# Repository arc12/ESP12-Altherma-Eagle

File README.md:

# ESP12 PCB for ESPAltherma

## Power
The normal use case, i.e. operating in the HP, is for the HP to power the board. JP1 is effectively an emergency disconnect feature and is normally on.

## Flashing
The firmware supports "Over The Air" updating but initial flashing will be via the Serial header. This initial flashing should be done without X10A being connected to the heat pump.

If testing with a 5V USB/Serial adapter attached to X10A then JP2 should be removed.

## Runtime Switches
__S1__ (Reset) - ESP-12 reset.
__S2__ is optional, see notes on Serial, below

## Headers
### Serial
UART pins and power, intended for initial flashing the device and diagnostic monitoring using a BT module. When using a Bluetooth serial monitor, JP2 should be on, to supply it with power. Note that the pin labels are to match those on the serial device, rather than being those of the ESP8622.  3.3V logic must be used.

Note that, if the DTR and RTS signals are connected (and D2 installed), then the PlatformIO monitor (or any other serial interaction which is not bootloading) must be configured as follows (add to platformio.ini), otherwise attempts to use the Monitor cause the board to hang (recovers if the monitor is killed):
```
monitor_rts = 0
monitor_dtr = 0
```

If DTR is not available on the USB/Serial adapter, install S2 and R16 and cut through SJ1 and SJ2 for manual boot-loader trigger.
__S2__ (Flash) -  Reset will trigger the boot loader if this switch is held on (i.e. flashing is done by holding S2 and then pressing/releasing S1). Once the new programme has been flashed, S1 (reset) must be done manually.

## Off-board "Thermo" Relay
See the ESPAltherma documentation for notes on the use of a relay to simulate a thermostat in order to on/off control the HP. This is a mains voltage relay AFAIK and in the interest of safety I decided to keep mains off the PCB. Hence there is a header to connect the GPIO to an off-board relay (which should ideally have an opto-coupler and suitable isolation gaps). A solder-jumper (SJ3) is used to allow selection of 3.3V or 5V for the header.

## Options
### LED Signalling
The battery of LEDs and associated Rs, plus JP3 allow for the output states to be signalled. JP3 allows for this signalling to be disconnected/reconnected as required. The external "thermo" relay is assumed to have its own signal.

If the LEDs are not fitted then the pad nearest to "L1", "SG1", etc may be used as a test point.

The ESP-12 modules have a LED on GPIO2, which is used as a "booted and running OK" signal.

### Bluetooth Monitoring
May be achieved by connecting a BT Serial module to the Serial header. Connect JP2 to power the module. NB this is 3.3V.

### Smart Grid OR Power Limitation
These two features use the same GPIO; only fit one set of components!

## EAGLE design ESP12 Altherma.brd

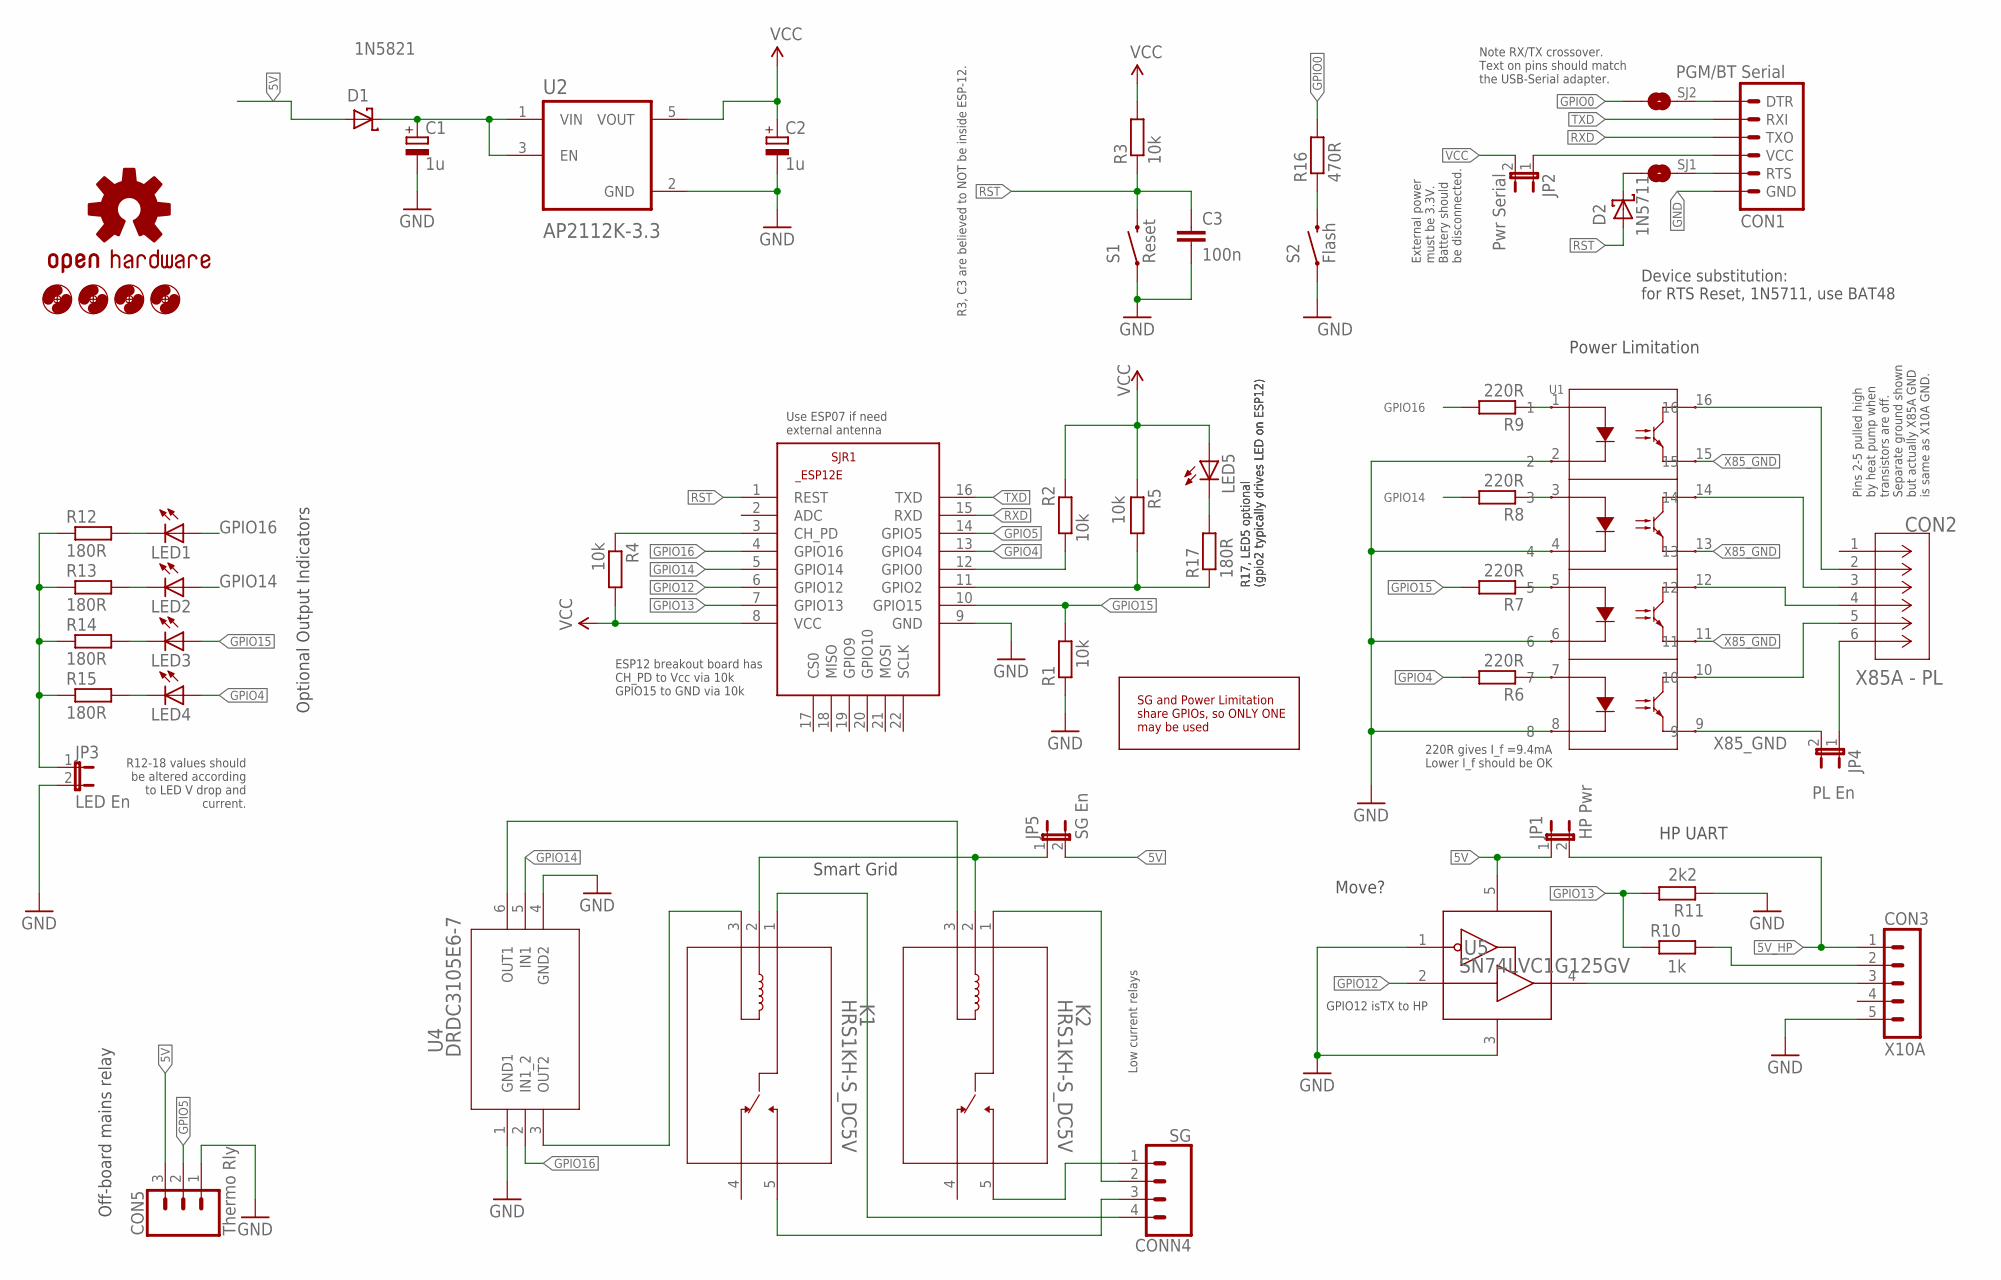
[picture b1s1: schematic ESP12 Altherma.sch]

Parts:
C1, C2: 1u; E2,5-5
C3: 100n; 1206
CON1: PGM/BT Serial; 1X06-KIT
CON2: X85A - PL; CONN_B06B-PASK_JST
CON3: X10A; B5B-EH-A
CON5: Thermo Rly; 1X03
CONN4: SG; 1X04
D1: 1N5821; DO201-15
D2: 1N5711; DO35-7
H1, H2, H3, H4: MOUNT-HOLE3.2; 3,2
JP1: HP Pwr; 1X02
JP2: Pwr Serial; 1X02
JP3: LED En; 1X02
JP4: PL En; 1X02
JP5: SG En; 1X02
K1, K2: HRS1KH-S_DC5V; HRS1KH-S_DC5V_MTC
LED1, LED2, LED3, LED4, LED5: LED1206; LED-1206
LOGO1: OSHW-LOGOM; OSHW-LOGO-M
R1, R2, R3, R4, R5: 10k; 1206
R6, R7, R8, R9: 220R; 1206
R10: 1k; 1206
R11: 2k2; 1206
R12, R13, R14, R15, R17: 180R; 1206
R16: 470R; 0204/7
S1: Reset; TACTILE-PTH
S2: Flash; TACTILE-PTH
SJ1, SJ2: SOLDERJUMPERTRACE; SJ_2S-TRACE
SJR1: ESP8266-12EESP8266-ESP12E-X; ESP8266-ESP12E0-NKE
U1: TLP291-4; SO16_TOS
U2: AP2112K-3.3; SOT95P285X140-5N
U4: DRDC3105E6-7; SOT26-DI_DIO-M
U5: SN74LVC1G125GV; DBV0005A_L

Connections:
5V: CON5.3, D1.A, JP1.1, JP5.2, U5.5 (VCC)
5V_HP: CON3.1, JP1.2
GND: C1.-, C2.-, C3.2, CON1.1 (GND), CON3.5, CON5.1, JP3.2, R1.1, R11.1, S1.1, S2.1, SJR1.9 (GND), U1.2, U1.4, U1.6, U1.8, U2.2 (GND), U4.1 (GND1), U4.4 (GND2), U5.1 (OE_N), U5.3 (GND)
GPIO0: R2.1, R16.2, SJ2.1, SJR1.12 (GPIO0)
GPIO2: R5.2, R17.1, SJR1.11 (GPIO2)
GPIO4: LED4.A, R6.2, SJR1.13 (GPIO4)
GPIO5: CON5.2, SJR1.14 (GPIO5)
GPIO12: SJR1.6 (GPIO12), U5.2 (A)
GPIO13: R10.1, R11.2, SJR1.7 (GPIO13)
GPIO14: LED2.A, R8.2, SJR1.5 (GPIO14), U4.5 (IN1)
GPIO15: LED3.A, R1.2, R7.2, SJR1.10 (GPIO15)
GPIO16: LED1.A, R9.2, SJR1.4 (GPIO16), U4.2 (IN1_2)
unnamed: R16.1, S2.3 (2)
unnamed: R9.1, U1.1
unnamed: CON2.3, U1.14
unnamed: JP3.1, R12.1, R13.1, R14.1, R15.1
unnamed: CON1.2 (RTS), SJ1.2
unnamed: JP5.1, K1.2, K2.2
unnamed: LED3.C, R14.2
unnamed: C1.+, D1.C, U2.1 (VIN), U2.3 (EN)
unnamed: CON1.3 (VCC), JP2.1
unnamed: CON1.6 (DTR), SJ2.2
unnamed: CON2.5, U1.10
unnamed: CON2.4, U1.12
unnamed: CON2.2, U1.16
unnamed: D2.C, SJ1.1
unnamed: LED4.C, R15.2
unnamed: R4.1, SJR1.3 (CH_PD)
unnamed: R6.1, U1.7
unnamed: R8.1, U1.3
unnamed: R7.1, U1.5
unnamed: CON3.3, U5.4 (Y)
unnamed: CON3.2, R10.2
unnamed: CONN4.1, K2.5
unnamed: CONN4.2, K2.1
unnamed: CONN4.3, K1.5
unnamed: CONN4.4, K1.1
unnamed: K1.3, U4.3 (OUT2)
unnamed: CON2.6, JP4.1
unnamed: LED5.C, R17.2
unnamed: K2.3, U4.6 (OUT1)
unnamed: LED1.C, R12.2
unnamed: LED2.C, R13.2
RST: C3.1, D2.A, R3.1, S1.3 (2), SJR1.1 (REST)
RXD: CON1.4 (TXO), SJR1.15 (RXD)
TXD: CON1.5 (RXI), SJR1.16 (TXD)
VCC: C2.+, JP2.2, LED5.A, R2.2, R3.2, R4.2, R5.1, SJR1.8 (VCC), U2.5 (VOUT)
X85_GND: JP4.2, U1.9, U1.11, U1.13, U1.15

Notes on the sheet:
R3, C3 are believed to NOT be inside ESP-12.
ESP12 breakout board has CH_PD to Vcc via 10k GPIO15 to GND via 10k
Note RX/TX crossover. Text on pins should match the USB-Serial adapter.
External power must be 3.3V. Battery should be disconnected.
R12-18 values should be altered according to LED V drop and current.
Device substitution: for RTS Reset, 1N5711, use BAT48
GPIO12 isTX to HP
Low current relays
Use ESP07 if need external antenna
Optional Output Indicators
Power Limitation
Smart Grid
HP UART
Off-board mains relay
220R gives I_f =9.4mA Lower I_f should be OK
Move?
Pins 2-5 pulled high by heat pump when transistors are off. Separate ground shown but actually X85A GND is same as X10A GND.
SG and Power Limitation share GPIOs, so ONLY ONE may be used
R17, LED5 optional (gpio2 typically drives LED on ESP12)

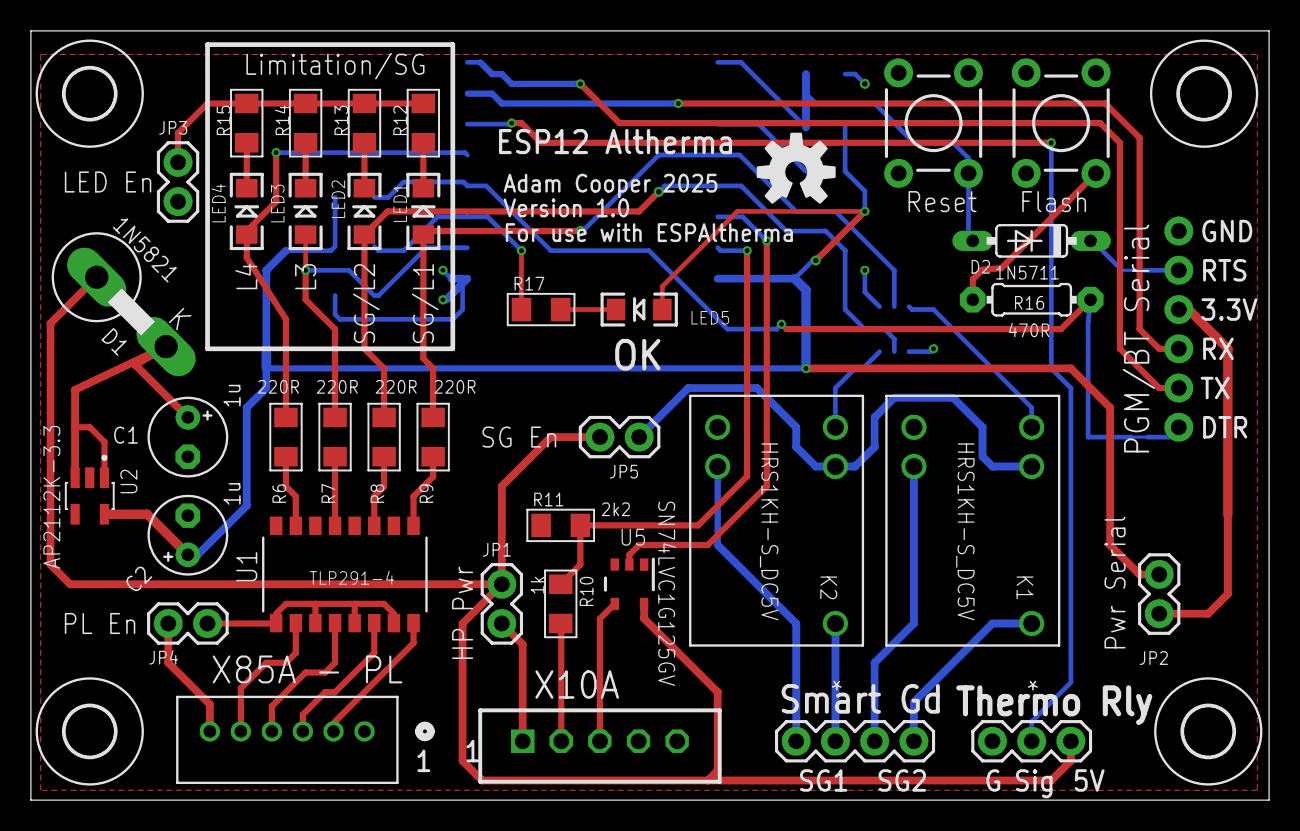
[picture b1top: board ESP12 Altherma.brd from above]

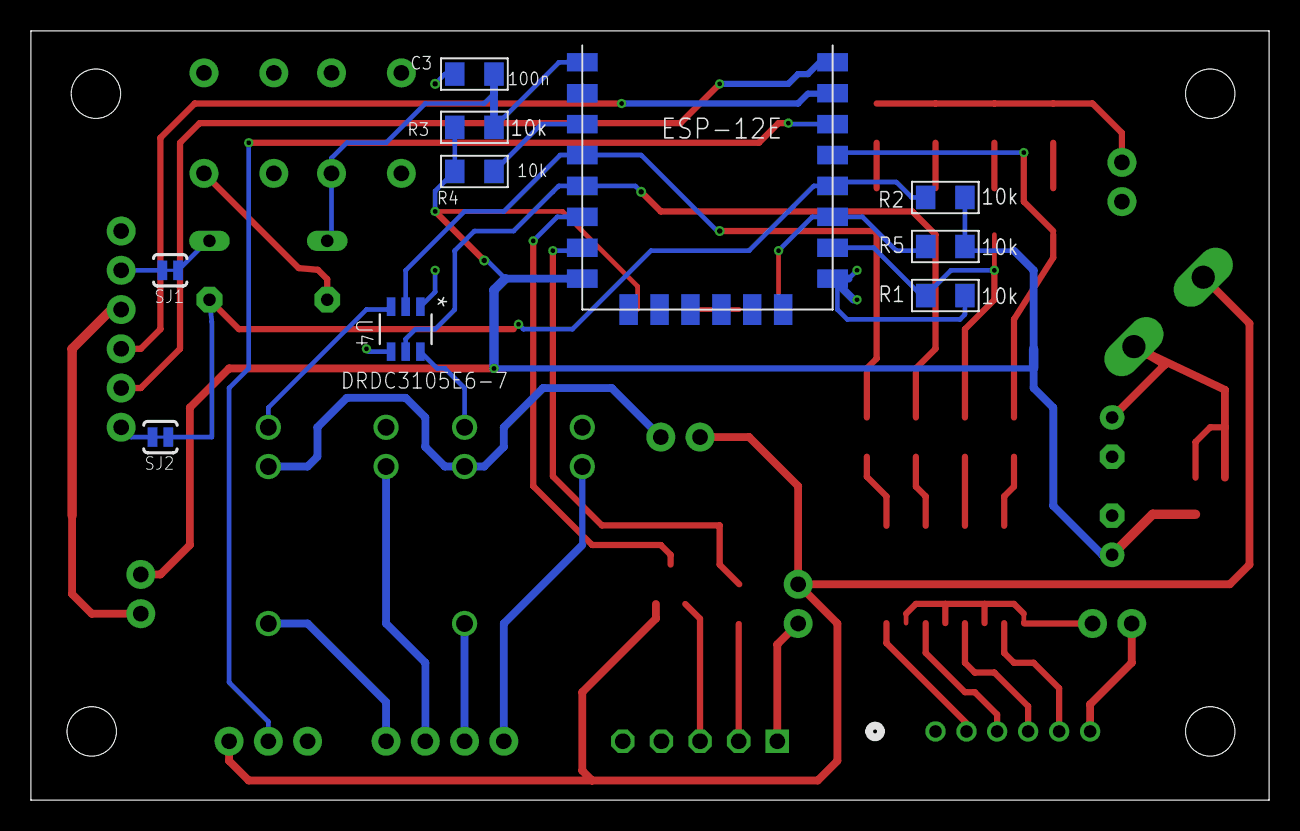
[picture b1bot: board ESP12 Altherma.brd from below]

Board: 2 copper layers, 80.1 x 49.8 mm, 53 parts (10 on the bottom side), 48 nets.

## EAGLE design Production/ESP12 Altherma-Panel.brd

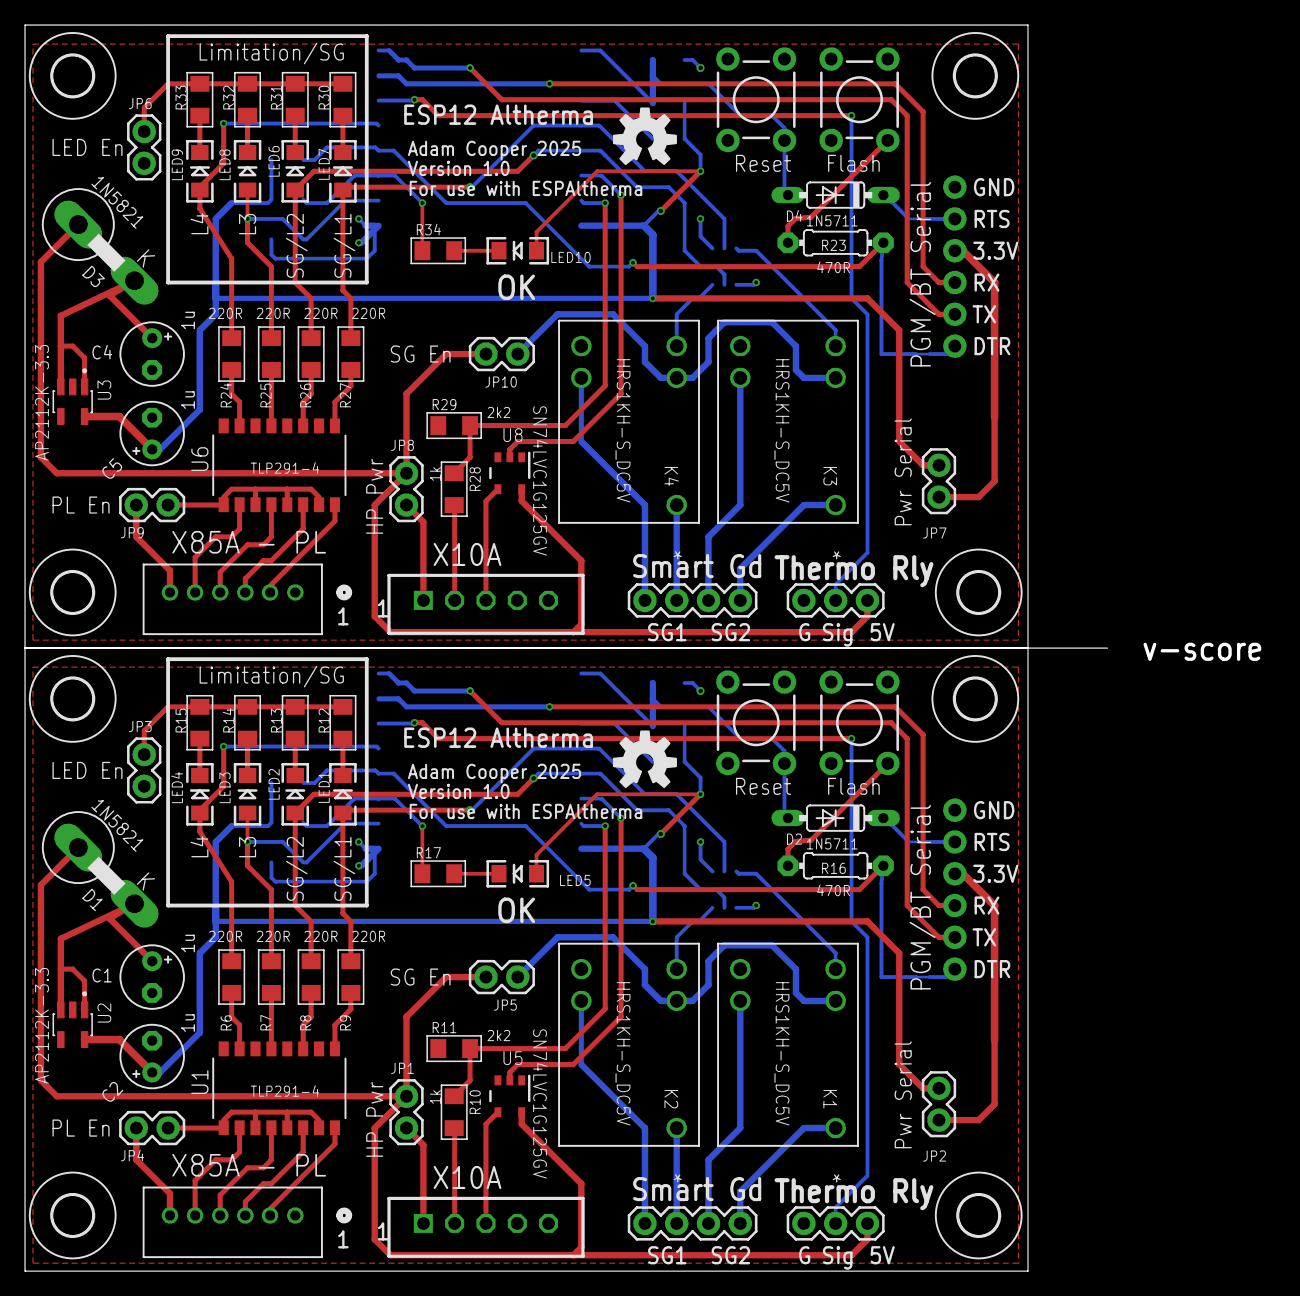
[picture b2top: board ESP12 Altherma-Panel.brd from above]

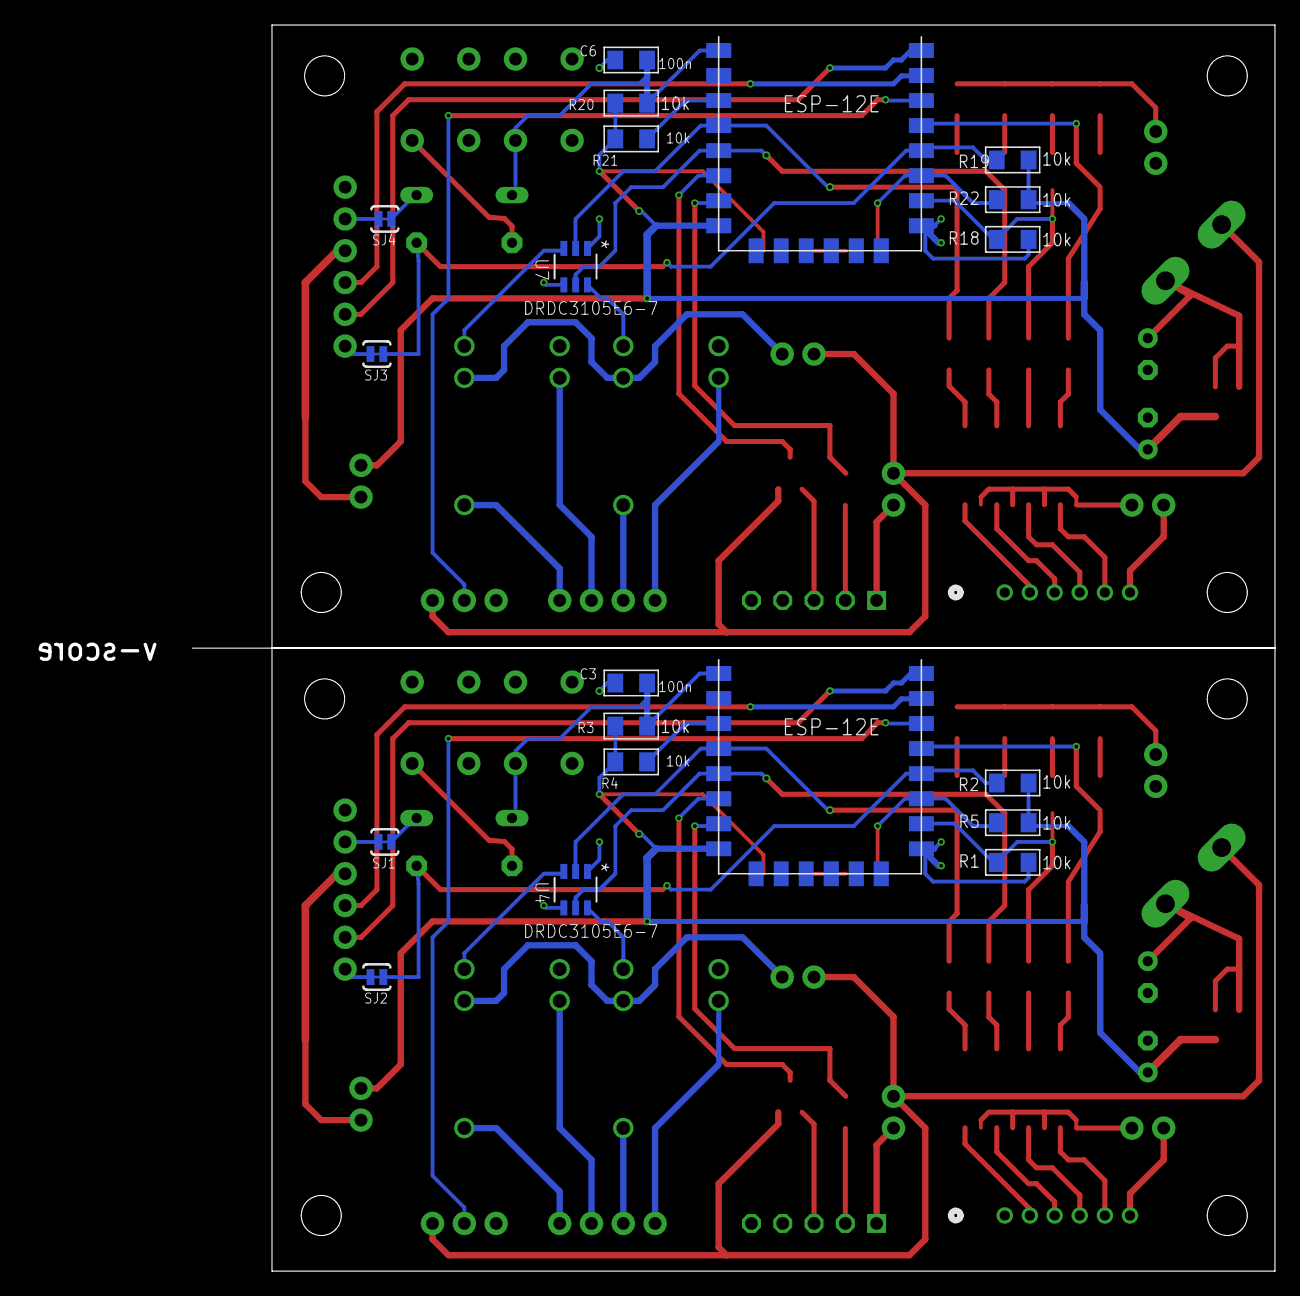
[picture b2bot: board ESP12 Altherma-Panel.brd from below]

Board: 2 copper layers, 99.9 x 99.6 mm, 106 parts (20 on the bottom side), 96 nets.

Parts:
C1, C2, C4, C5: 1u; E2,5-5
C3, C6: 100n; 1206
CON1, CON4: PGM/BT Serial; 1X06-KIT
CON2, CON8: X85A - PL; CONN_B06B-PASK_JST
CON3, CON7: X10A; B5B-EH-A
CON5, CON6: Thermo Rly; 1X03
CONN1, CONN4: SG; 1X04
D1, D3: 1N5821; DO201-15
D2, D4: 1N5711; DO35-7
H1, H2, H3, H4, H5, H6, H7, H8: MOUNT-HOLE3.2; 3,2
JP1, JP8: HP Pwr; 1X02
JP2, JP7: Pwr Serial; 1X02
JP3, JP6: LED En; 1X02
JP4, JP9: PL En; 1X02
JP5, JP10: SG En; 1X02
K1, K2, K3, K4: HRS1KH-S_DC5V; HRS1KH-S_DC5V_MTC
LED1, LED2, LED3, LED4, LED5, LED6, LED7, LED8, LED9, LED10: LED-1206
LOGO1, LOGO2: OSHW-LOGOM; OSHW-LOGO-M
R1, R2, R3, R4, R5, R18, R19, R20, R21, R22: 10k; 1206
R6, R7, R8, R9, R24, R25, R26, R27: 220R; 1206
R10, R28: 1k; 1206
R11, R29: 2k2; 1206
R12, R13, R14, R15, R17, R30, R31, R32, R33, R34: 180R; 1206
R16, R23: 470R; 0204/7
S1, S3: Reset; TACTILE-PTH
S2, S4: Flash; TACTILE-PTH
SJ1, SJ2, SJ3, SJ4: SOLDERJUMPERTRACE; SJ_2S-TRACE
SJR1, SJR2: ESP8266-ESP12E0-NKE
U1, U6: TLP291-4; SO16_TOS
U2, U3: AP2112K-3.3; SOT95P285X140-5N
U4, U7: DRDC3105E6-7; SOT26-DI_DIO-M
U5, U8: SN74LVC1G125GV; DBV0005A_L

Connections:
5V: CON5.3, D1.A, JP1.1, JP5.2, U5.5
5V1: CON6.3, D3.A, JP8.1, JP10.2, U8.5
5V_HP: CON3.1, JP1.2
5V_HP1: CON7.1, JP8.2
GND: C1.-, C2.-, C3.2, CON1.1, CON3.5, CON5.1, JP3.2, R1.1, R11.1, S1.1, S2.1, SJR1.9, U1.2, U1.4, U1.6, U1.8, U2.2, U4.1, U4.4, U5.1, U5.3
GND1: C4.-, C5.-, C6.2, CON4.1, CON6.1, CON7.5, JP6.2, R18.1, R29.1, S3.1, S4.1, SJR2.9, U3.2, U6.2, U6.4, U6.6, U6.8, U7.1, U7.4, U8.1, U8.3
GPIO0: R2.1, R16.2, SJ2.1, SJR1.12
GPIO1: LED9.A, R24.2, SJR2.13
GPIO2: R5.2, R17.1, SJR1.11
GPIO3: CON6.2, SJR2.14
GPIO4: LED4.A, R6.2, SJR1.13
GPIO5: CON5.2, SJR1.14
GPIO6: SJR2.6, U8.2
GPIO7: R28.1, R29.2, SJR2.7
GPIO8: LED6.A, R26.2, SJR2.5, U7.5
GPIO9: R19.1, R23.2, SJ3.1, SJR2.12
GPIO10: R22.2, R34.1, SJR2.11
GPIO11: LED7.A, R27.2, SJR2.4, U7.2
GPIO12: SJR1.6, U5.2
GPIO13: R10.1, R11.2, SJR1.7
GPIO14: LED2.A, R8.2, SJR1.5, U4.5
GPIO15: LED3.A, R1.2, R7.2, SJR1.10
GPIO16: LED1.A, R9.2, SJR1.4, U4.2
GPIO17: LED8.A, R18.2, R25.2, SJR2.10
unnamed: R16.1, S2.3
unnamed: R9.1, U1.1
unnamed: CON2.3, U1.14
unnamed: JP3.1, R12.1, R13.1, R14.1, R15.1
unnamed: CON1.2, SJ1.2
unnamed: JP5.1, K1.2, K2.2
unnamed: LED3.C, R14.2
unnamed: C1.+, D1.C, U2.1, U2.3
unnamed: CON1.3, JP2.1
unnamed: CON1.6, SJ2.2
unnamed: CON2.5, U1.10
unnamed: CON2.4, U1.12
unnamed: CON2.2, U1.16
unnamed: D2.C, SJ1.1
unnamed: LED4.C, R15.2
unnamed: R4.1, SJR1.3
unnamed: R6.1, U1.7
unnamed: R8.1, U1.3
unnamed: R7.1, U1.5
unnamed: CON3.3, U5.4
unnamed: CON3.2, R10.2
unnamed: CONN4.1, K2.5
unnamed: CONN4.2, K2.1
unnamed: CONN4.3, K1.5
unnamed: CONN4.4, K1.1
unnamed: K1.3, U4.3
unnamed: CON2.6, JP4.1
unnamed: LED5.C, R17.2
unnamed: K2.3, U4.6
unnamed: R21.1, SJR2.3
unnamed: R23.1, S4.3
unnamed: C4.+, D3.C, U3.1, U3.3
unnamed: CON4.3, JP7.1
unnamed: CON4.6, SJ3.2
unnamed: CON4.2, SJ4.2
unnamed: D4.C, SJ4.1
unnamed: CON8.5, U6.10
unnamed: CON8.4, U6.12
unnamed: LED1.C, R12.2
unnamed: LED2.C, R13.2
unnamed: CON8.3, U6.14
unnamed: CON8.2, U6.16
unnamed: R24.1, U6.7
unnamed: R27.1, U6.1
unnamed: R26.1, U6.3
unnamed: R25.1, U6.5
unnamed: CON7.3, U8.4
unnamed: CON7.2, R28.2
unnamed: CONN1.1, K4.5
unnamed: CONN1.3, K3.5
unnamed: CONN1.2, K4.1
unnamed: CONN1.4, K3.1
unnamed: K3.3, U7.3
unnamed: K4.3, U7.6
unnamed: JP6.1, R30.1, R31.1, R32.1, R33.1
unnamed: LED8.C, R32.2
unnamed: LED9.C, R33.2
unnamed: LED7.C, R30.2
unnamed: LED6.C, R31.2
unnamed: CON8.6, JP9.1
unnamed: JP10.1, K3.2, K4.2
unnamed: LED10.C, R34.2
RST: C3.1, D2.A, R3.1, S1.3, SJR1.1
RST1: C6.1, D4.A, R20.1, S3.3, SJR2.1
RXD: CON1.4, SJR1.15
RXD1: CON4.4, SJR2.15
TXD: CON1.5, SJR1.16
TXD1: CON4.5, SJR2.16
VCC: C2.+, JP2.2, LED5.A, R2.2, R3.2, R4.2, R5.1, SJR1.8, U2.5
VCC1: C5.+, JP7.2, LED10.A, R19.2, R20.2, R21.2, R22.1, SJR2.8, U3.5
X85_GND: JP4.2, U1.9, U1.11, U1.13, U1.15
X85_GND1: JP9.2, U6.9, U6.11, U6.13, U6.15

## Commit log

2024-03-30 Complete prototype version, not properly checked and circuit not tested, let alone a PCB made!
2025-02-09 shorten board. share GPIO for LP and SG. use JST connectors. tidy needless complexity
2025-02-09 change esp12 to version without Restrict layer so I can panelise
2025-02-09 Provisionally final tweaks prior to attempting panelisation
2025-02-10 I think this is v1.0. This commit free of any panelisation guff.
2025-02-10 silk tweak!
2025-02-10 Added layers 125/6 in BRD. Added panelised BRD.
2025-02-10 gerbers sent to Seeed for PCB fab
2025-03-24 clean up schematic

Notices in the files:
parts and their libraries:
SparkFun-Passives: Licensing: CC v3.0 Share-Alike You are welcome to use this library for commercial purposes.
SparkFun-Connectors: Licensing: Creative Commons ShareAlike 4.0 International - https://creativecommons.org/licenses/by-sa/4.0
con-jst-eh: Copyright (C) 2016, Bob Starr
